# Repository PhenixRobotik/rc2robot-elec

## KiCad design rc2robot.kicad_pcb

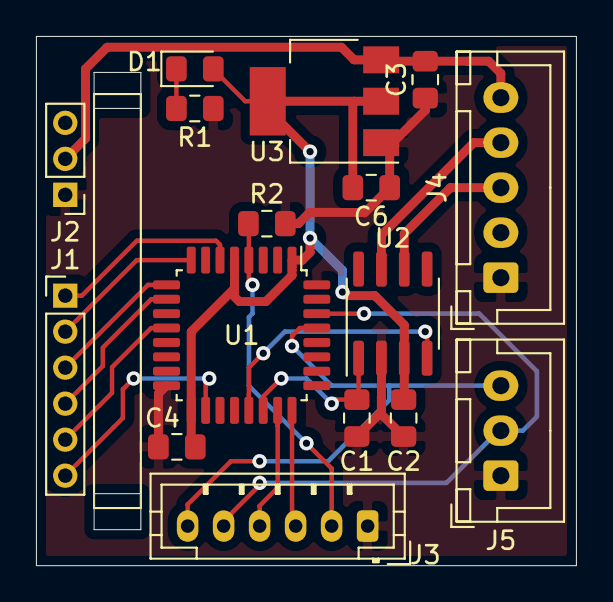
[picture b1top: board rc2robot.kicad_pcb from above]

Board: 2 copper layers, 30.0 x 29.4 mm, 16 parts (0 on the bottom side), 19 nets.

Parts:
C1: 100p; C_0805_2012Metric_Pad1.15x1.40mm_HandSolder
C2: 100n; C_0805_2012Metric_Pad1.15x1.40mm_HandSolder
C3, C6: 10u; C_0805_2012Metric_Pad1.15x1.40mm_HandSolder
C4: 1u; C_0805_2012Metric_Pad1.15x1.40mm_HandSolder
D1: GREEN; LED_0805_2012Metric_Pad1.15x1.40mm_HandSolder
J1: Conn_01x06; PinHeader_1x06_P2.00mm_Vertical
J2: Conn_01x03; PinHeader_1x03_P2.00mm_Vertical
J3: Conn_Debug; JST_PH_B6B-PH-K_1x06_P2.00mm_Vertical
J4: CAN_conn; JST_XH_B5B-XH-A_1x05_P2.50mm_Vertical
J5: Conn_01x03; JST_XH_B3B-XH-A_1x03_P2.50mm_Vertical
R1: 230; R_0805_2012Metric_Pad1.15x1.40mm_HandSolder
R2: 10k; R_0805_2012Metric_Pad1.15x1.40mm_HandSolder
U1: STM32F303K8Tx; LQFP-32_7x7mm_P0.8mm
U2: TCAN332; SOIC-8_3.9x4.9mm_P1.27mm
U3: LD1117S33TR_SOT223; SOT-223-3_TabPin2

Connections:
+3V3: C2.1, C4.2, C6.1, D1.2, U1.1, U1.5, U1.17, U2.3, U3.2
+7.5V: C3.1, J2.2, J4.5, U3.3
/Aile: J1.2, U1.8
/Aux1: J1.6, U1.18
/CAN_RX: U1.21, U2.4
/CAN_TX: C1.1, U1.22, U2.1
/Elev: J1.3, U1.9
/Gear: J1.5, U1.12
/Rudd: J1.4, U1.10
/TCK: J3.3, U1.24
/TMS: J3.4, U1.23
/Thro: J1.1, U1.6
/USART1_RX: J3.5, J5.2, U1.30
/USART1_TX: J3.6, J5.3, U1.29
/~RST: J3.2, R2.1, U1.4
GND: C1.2, C2.2, C3.2, C4.1, C6.2, J2.1, J3.1, J4.1, J5.1, R1.2, R2.2, U1.16, U1.32, U2.2, U3.1
unnamed: D1.1, R1.1
unnamed: J4.3, U2.6
unnamed: J4.4, U2.7

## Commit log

2019-11-07 Add base of board$
2019-11-08 finish board
